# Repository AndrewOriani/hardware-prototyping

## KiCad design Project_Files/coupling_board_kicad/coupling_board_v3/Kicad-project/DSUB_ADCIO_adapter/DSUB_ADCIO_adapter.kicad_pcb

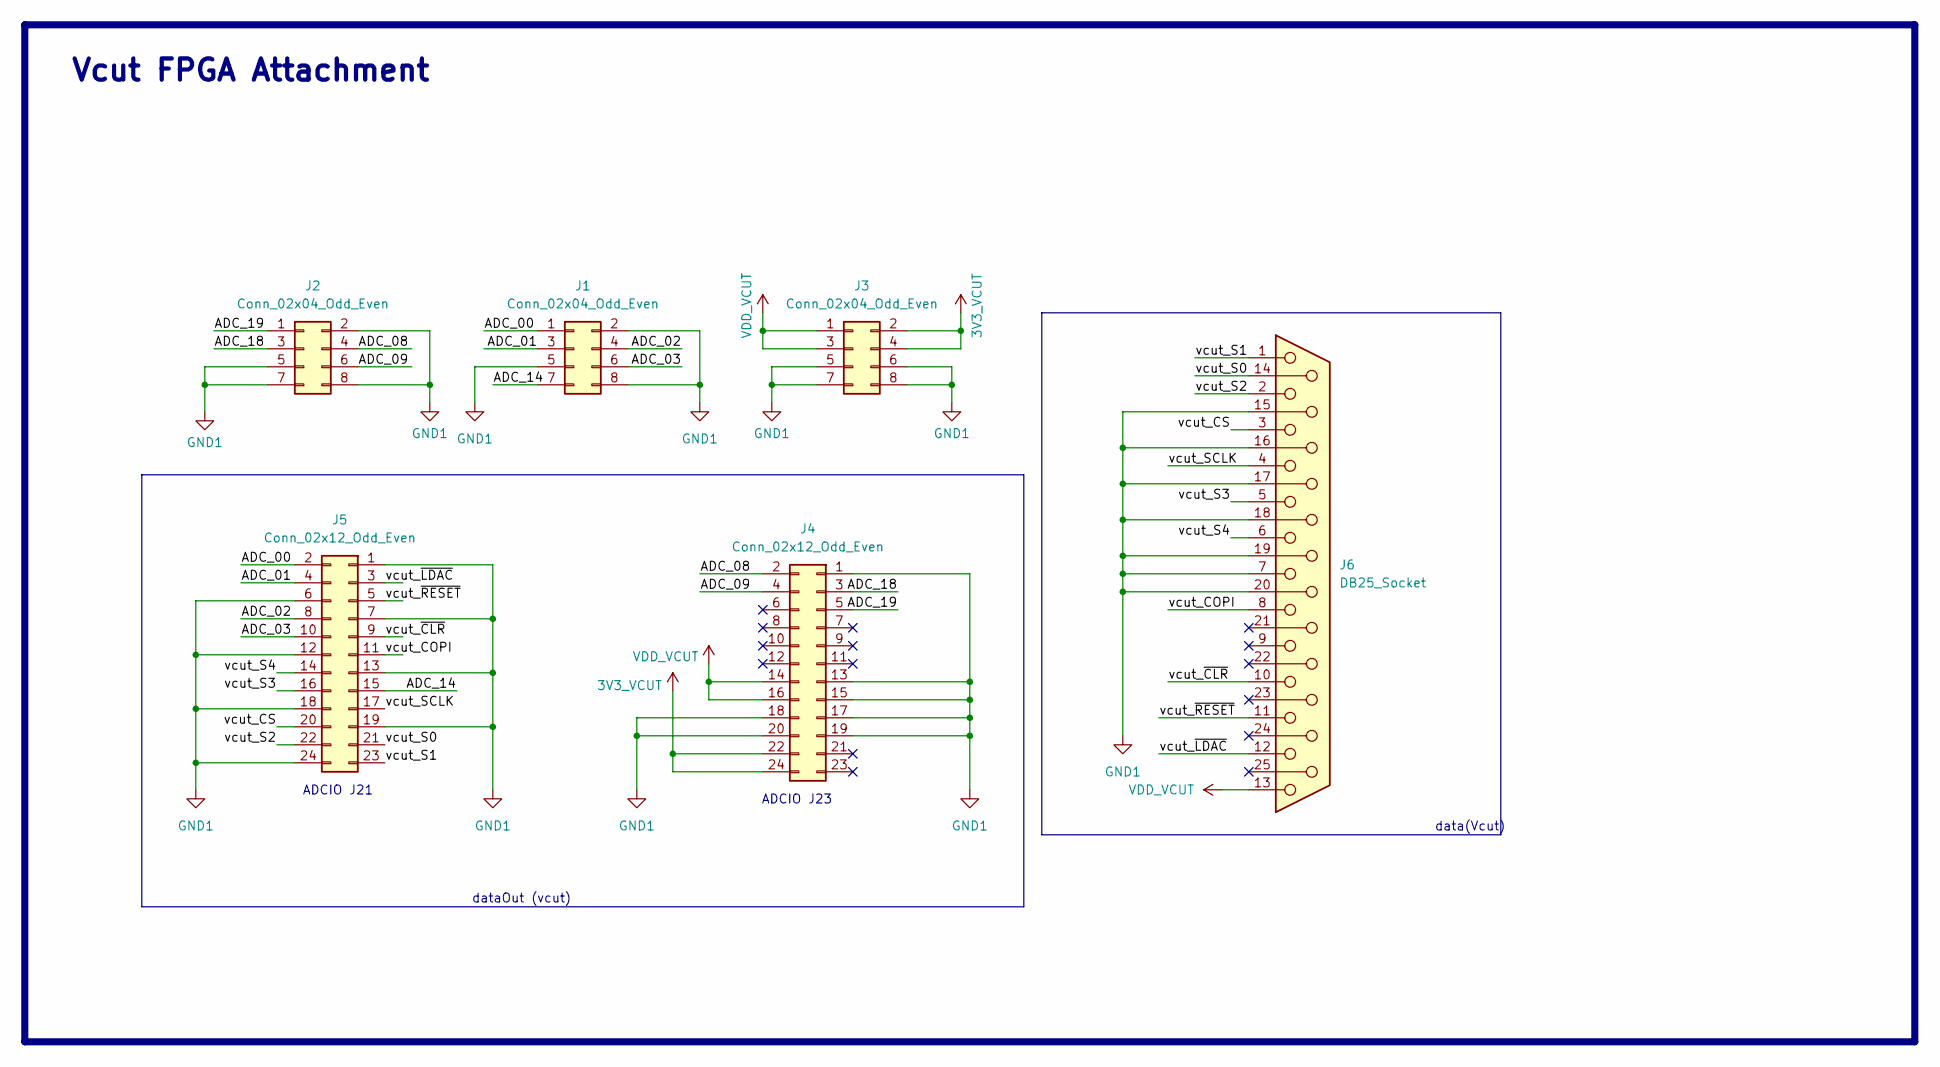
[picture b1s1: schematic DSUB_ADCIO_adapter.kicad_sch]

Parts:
J1, J2, J3: Conn_02x04_Odd_Even; PinSocket_2x04_P2.54mm_Vertical
J4, J5: Conn_02x12_Odd_Even; PinHeader_2x12_P2.54mm_Vertical; JLCPCB Part # C132440
J6: DB25_Socket; DSUB-TH_DS1034-25FUNSI44

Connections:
3V3_VCUT: J3.2, J3.4, J4.22, J4.24
/ADC_00: J1.1, J5.2
/ADC_01: J1.3, J5.4
/ADC_02: J1.4, J5.8
/ADC_03: J1.6, J5.10
/ADC_08: J2.4, J4.2
/ADC_09: J2.6, J4.4
/ADC_14: J1.7, J5.15
/ADC_18: J2.3, J4.3
/ADC_19: J2.1, J4.5
/vcut_COPI: J5.11, J6.8
/vcut_CS: J5.20, J6.3
/vcut_S0: J5.21, J6.14
/vcut_S1: J5.23, J6.1
/vcut_S2: J5.22, J6.2
/vcut_S3: J5.16, J6.5
/vcut_S4: J5.14, J6.6
/vcut_SCLK: J5.17, J6.4
/vcut_~CLR: J5.9, J6.10
/vcut_~LDAC: J5.3, J6.12
/vcut_~RESET: J5.5, J6.11
GND1: J1.2, J1.5, J1.8, J2.2, J2.5, J2.7, J2.8, J3.5, J3.6, J3.7, J3.8, J4.1, J4.13, J4.15, J4.17, J4.18, J4.19, J4.20, J5.1, J5.6, J5.7, J5.12, J5.13, J5.18, J5.19, J5.24, J6.7, J6.15, J6.16, J6.17, J6.18, J6.19, J6.20
VDD_VCUT: J3.1, J3.3, J4.14, J4.16, J6.13

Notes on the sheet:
ADCIO J23
data(Vcut)
ADCIO J21
Vcut FPGA Attachment
dataOut (vcut)

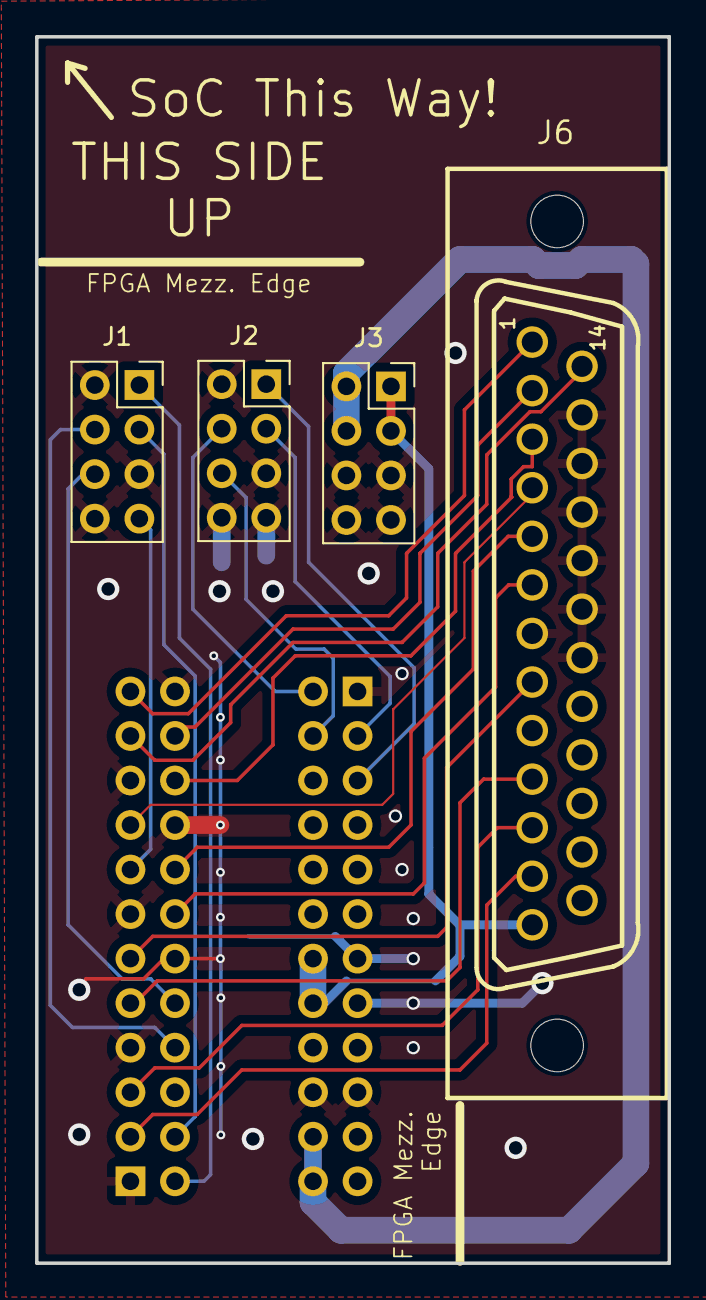
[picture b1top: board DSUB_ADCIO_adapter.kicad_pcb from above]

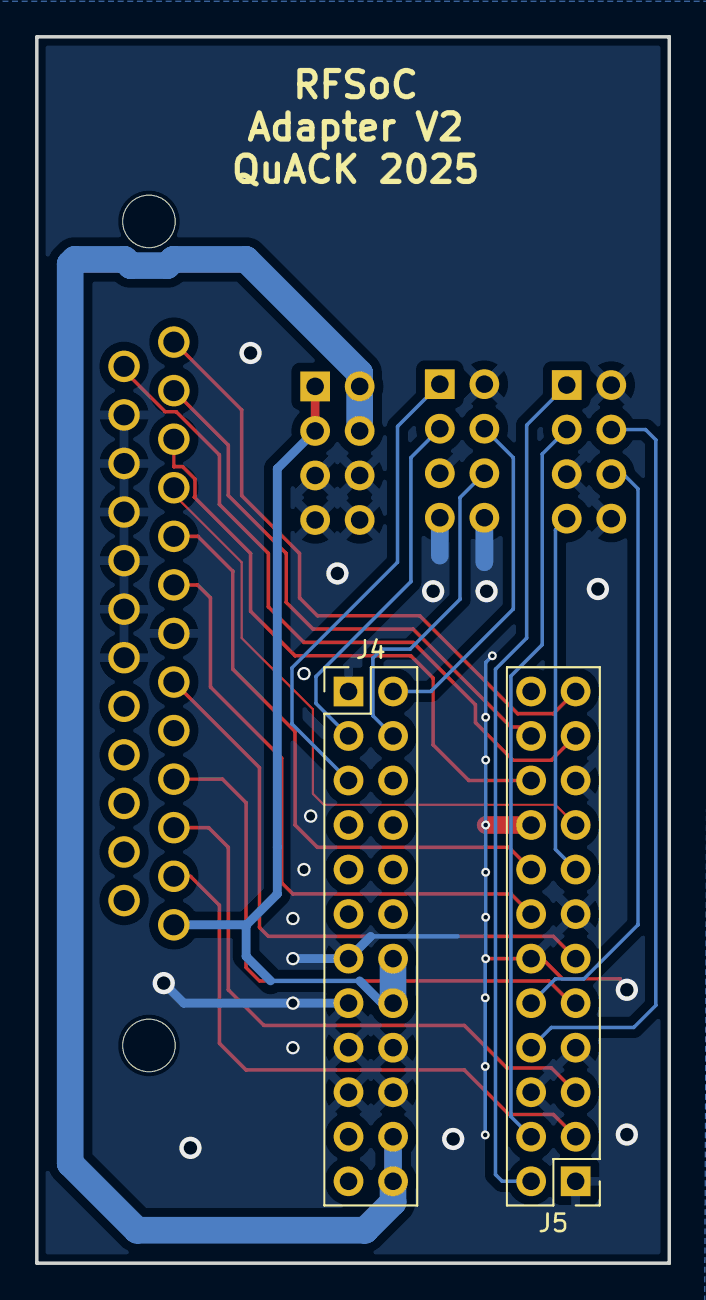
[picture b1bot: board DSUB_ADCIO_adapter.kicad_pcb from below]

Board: 2 copper layers, 36.1 x 70.0 mm, 6 parts (2 on the bottom side), 23 nets.

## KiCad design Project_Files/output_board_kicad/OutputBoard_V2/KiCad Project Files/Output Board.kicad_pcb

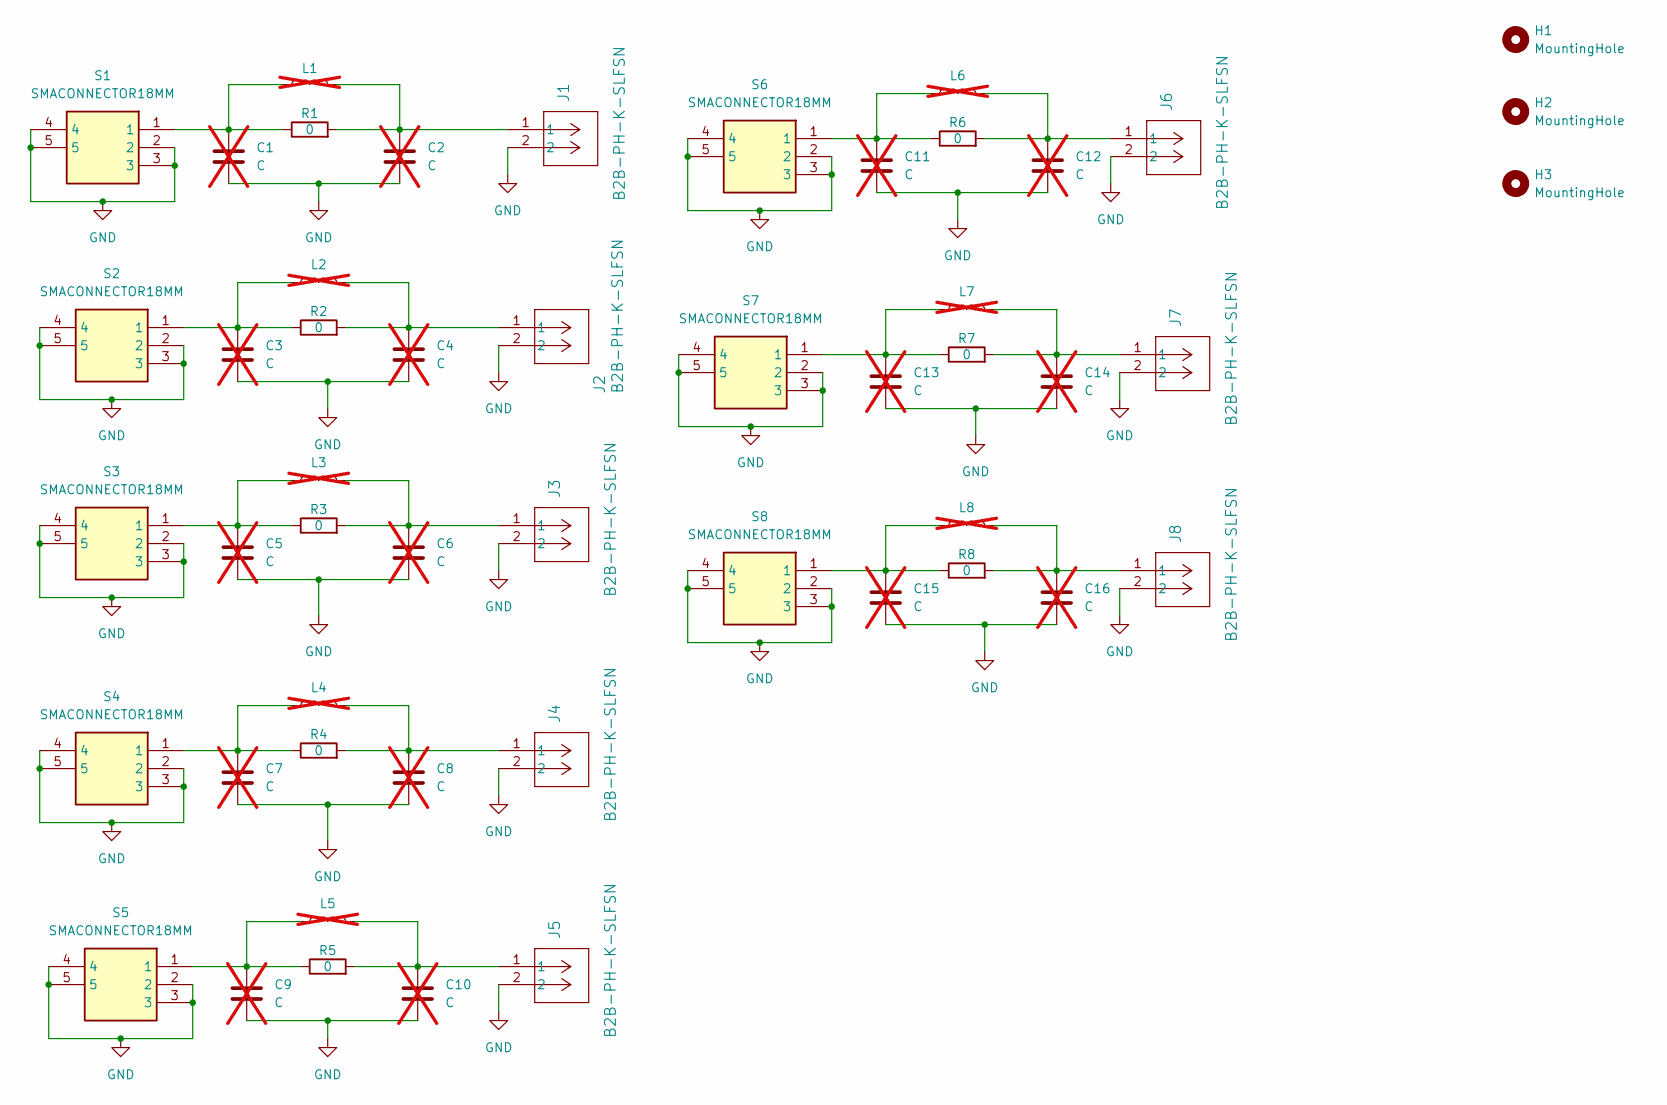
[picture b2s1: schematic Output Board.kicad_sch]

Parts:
C1, C2, C3, C4, C5, C6, C7, C8, C9, C10, C11, C12, C13, C14, C15, C16: C; C_0805_2012Metric; not fitted
H1, H2, H3: MountingHole; MountingHole_3mm
J1, J2, J3, J4, J5, J6, J7, J8: B2B-PH-K-SLFSN; CONN_B2B-PH-K-SLFSN_JST
L1, L2, L3, L4, L5, L6, L7, L8: L; IND_1537R_API; not fitted
R1, R2, R3, R4, R5, R6, R7, R8: 0; R_0805_2012Metric
S1, S2, S3, S4, S5, S6, S7, S8: SMACONNECTOR18MM; Mouser Part Number 471-SMACONNECTOR18MM

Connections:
GND: C1.2, C2.2, C3.2, C4.2, C5.2, C6.2, C7.2, C8.2, C9.2, C10.2, C11.2, C12.2, C13.2, C14.2, C15.2, C16.2, J1.2, J2.2, J3.2, J4.2, J5.2, J6.2, J7.2, J8.2, S1.2, S1.3, S1.4, S1.5, S2.2, S2.3, S2.4, S2.5, S3.2, S3.3, S3.4, S3.5, S4.2, S4.3, S4.4, S4.5, S5.2, S5.3, S5.4, S5.5, S6.2, S6.3, S6.4, S6.5, S7.2, S7.3, S7.4, S7.5, S8.2, S8.3, S8.4, S8.5
unnamed: C1.1, L1.1, R1.1, S1.1
unnamed: C2.1, J1.1, L1.2, R1.2
unnamed: C3.1, L2.1, R2.1, S2.1
unnamed: C4.1, J2.1, L2.2, R2.2
unnamed: C5.1, L3.1, R3.1, S3.1
unnamed: C6.1, J3.1, L3.2, R3.2
unnamed: C7.1, L4.1, R4.1, S4.1
unnamed: C8.1, J4.1, L4.2, R4.2
unnamed: C9.1, L5.1, R5.1, S5.1
unnamed: C10.1, J5.1, L5.2, R5.2
unnamed: C11.1, L6.1, R6.1, S6.1
unnamed: C12.1, J6.1, L6.2, R6.2
unnamed: C13.1, L7.1, R7.1, S7.1
unnamed: C14.1, J7.1, L7.2, R7.2
unnamed: C15.1, L8.1, R8.1, S8.1
unnamed: C16.1, J8.1, L8.2, R8.2

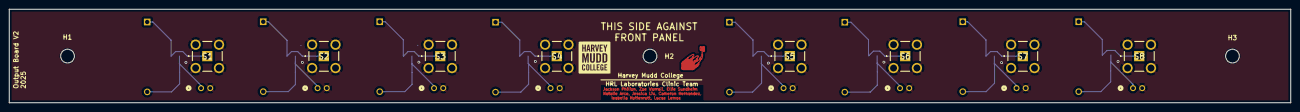
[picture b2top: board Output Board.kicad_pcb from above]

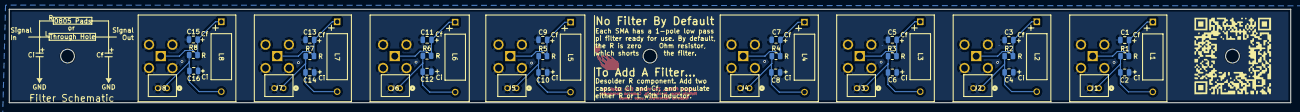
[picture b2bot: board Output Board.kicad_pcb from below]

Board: 2 copper layers, 279.4 x 20.4 mm, 52 parts (40 on the bottom side), 17 nets.

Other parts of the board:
  : LOGO; Footprint_HMC

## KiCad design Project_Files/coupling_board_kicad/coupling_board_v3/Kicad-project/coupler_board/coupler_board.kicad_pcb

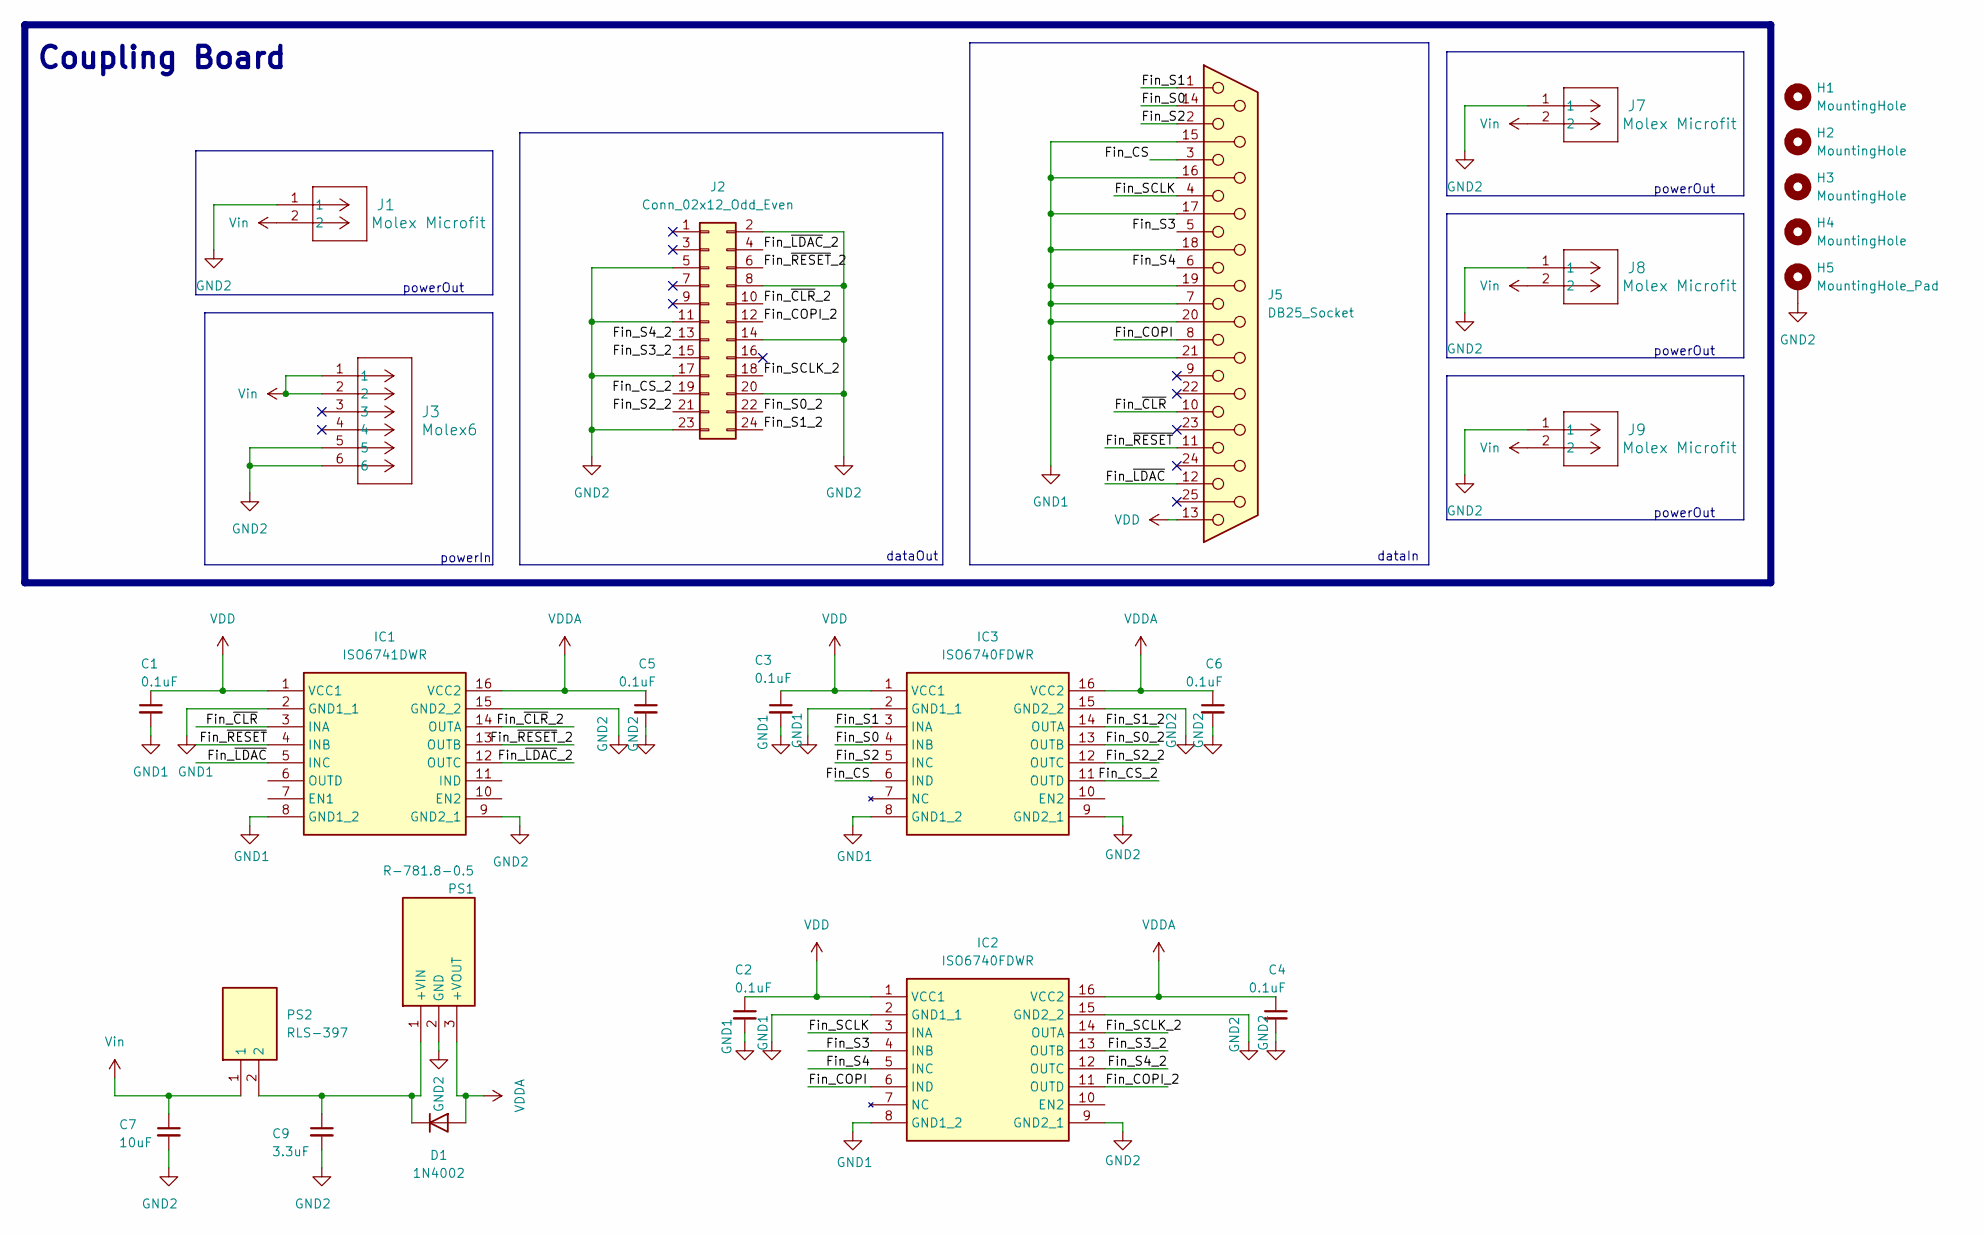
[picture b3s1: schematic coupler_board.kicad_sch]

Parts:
C1, C2, C3, C4, C5, C6: 0.1uF; C_0603_1608Metric
C7: 10uF; C_1210_3225Metric
C9: 3.3uF; C_1210_3225Metric
D1: 1N4002; D_DO-41_SOD81_P10.16mm_Horizontal
H1, H2, H3, H4: MountingHole; MountingHole_3.2mm_M3
H5: MountingHole_Pad; MountingHole_3.5mm_Pad
IC1: ISO6741DWR; SOIC127P1030X265-16N; Mouser Part Number 595-ISO6741DWR
IC2, IC3: ISO6740FDWR; SOIC127P1030X265-16N; Mouser Part Number 595-ISO6740FDWR
J1, J7, J8, J9: Molex Microfit; CONN_SD-43650-006_02_MOL
J2: Conn_02x12_Odd_Even; IDC-Header_2x12_P2.54mm_Vertical; JLCPCB Part # C132440
J3: Molex6; CONN_0039281063_5566-06A_MOL
J5: DB25_Socket; DSUB-TH_DS1034-25FUNSI44
PS1: R-781.8-0.5; R781805; Mouser Part Number 919-R-781.8-0.5
PS2: RLS-397; RLS397; Mouser Part Number 919-RLS-397

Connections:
/Fin_COPI: IC2.6 (IND), J5.8
/Fin_COPI_2: IC2.11 (OUTD), J2.12
/Fin_CS: IC3.6 (IND), J5.3
/Fin_CS_2: IC3.11 (OUTD), J2.19
/Fin_S0: IC3.4 (INB), J5.14
/Fin_S0_2: IC3.13 (OUTB), J2.22
/Fin_S1: IC3.3 (INA), J5.1
/Fin_S1_2: IC3.14 (OUTA), J2.24
/Fin_S2: IC3.5 (INC), J5.2
/Fin_S2_2: IC3.12 (OUTC), J2.21
/Fin_S3: IC2.4 (INB), J5.5
/Fin_S3_2: IC2.13 (OUTB), J2.15
/Fin_S4: IC2.5 (INC), J5.6
/Fin_S4_2: IC2.12 (OUTC), J2.13
/Fin_SCLK: IC2.3 (INA), J5.4
/Fin_SCLK_2: IC2.14 (OUTA), J2.18
/Fin_~CLR: IC1.3 (INA), J5.10
/Fin_~CLR_2: IC1.14 (OUTA), J2.10
/Fin_~LDAC: IC1.5 (INC), J5.12
/Fin_~LDAC_2: IC1.12 (OUTC), J2.4
/Fin_~RESET: IC1.4 (INB), J5.11
/Fin_~RESET_2: IC1.13 (OUTB), J2.6
GND1: C1.2, C2.2, C3.2, IC1.2 (GND1_1), IC1.8 (GND1_2), IC2.2 (GND1_1), IC2.8 (GND1_2), IC3.2 (GND1_1), IC3.8 (GND1_2), J5.7, J5.15, J5.16, J5.17, J5.18, J5.19, J5.20, J5.21
GND2: C4.2, C5.2, C6.2, C7.2, C9.2, H5.1, IC1.9 (GND2_1), IC1.15 (GND2_2), IC2.9 (GND2_1), IC2.15 (GND2_2), IC3.9 (GND2_1), IC3.15 (GND2_2), J1.1, J2.2, J2.5, J2.8, J2.11, J2.14, J2.17, J2.20, J2.23, J3.5, J3.6, J7.1, J8.1, J9.1, PS1.2 (GND)
unnamed: C9.1, D1.1 (K), PS1.1 (+VIN), PS2.2
VDD: C1.1, C2.1, C3.1, IC1.1 (VCC1), IC2.1 (VCC1), IC3.1 (VCC1), J5.13
VDDA: C4.1, C5.1, C6.1, D1.2 (A), IC1.16 (VCC2), IC2.16 (VCC2), IC3.16 (VCC2), PS1.3 (+VOUT)
Vin: C7.1, J1.2, J3.1, J3.2, J7.2, J8.2, J9.2, PS2.1

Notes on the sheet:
powerOut
dataIn
dataOut
powerIn
Coupling Board

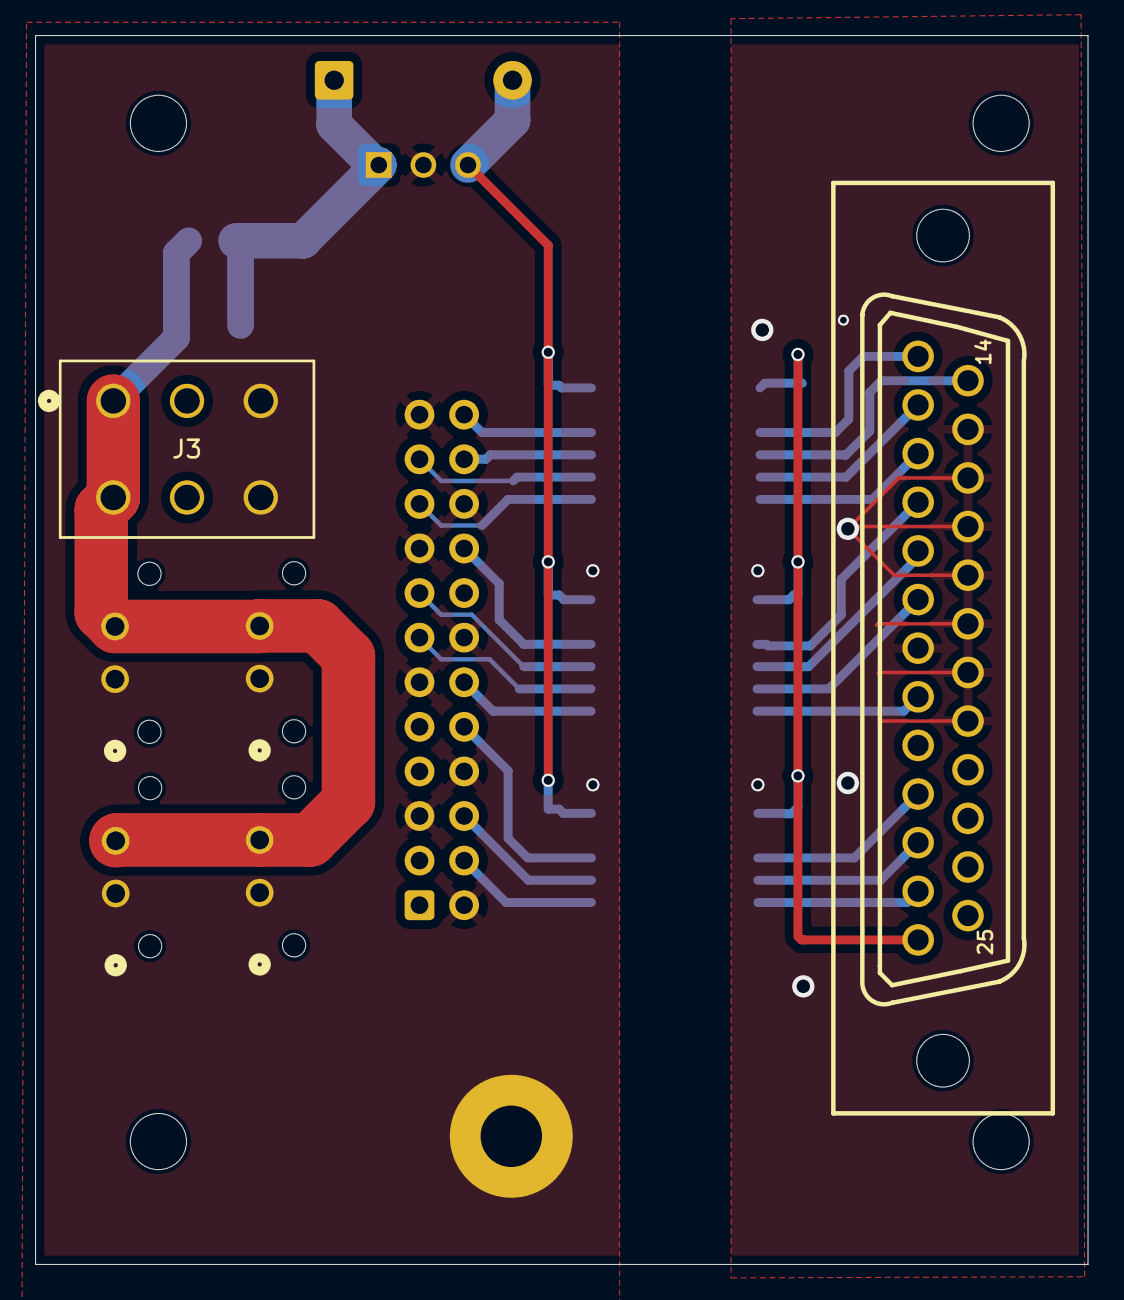
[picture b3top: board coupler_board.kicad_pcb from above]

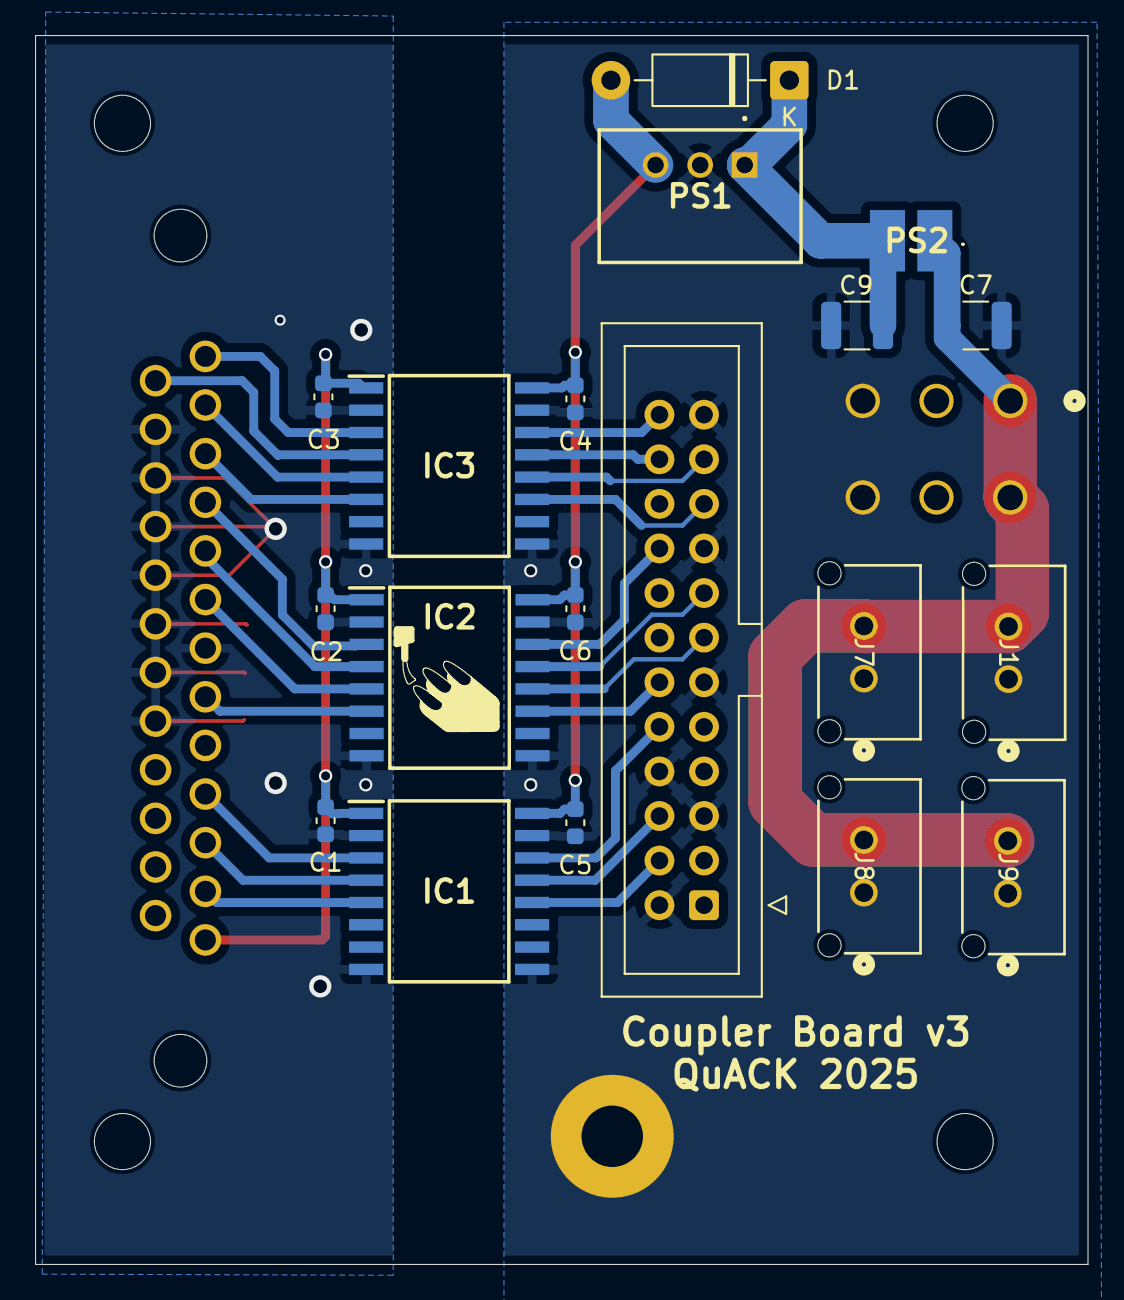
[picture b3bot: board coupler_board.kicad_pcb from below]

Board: 2 copper layers, 59.9 x 70.0 mm, 26 parts (19 on the bottom side), 28 nets.

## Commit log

2025-07-29 Added a v3 isolated version of coupler board, still need to add BOM and other project files
2025-08-04 Updated design files
2025-08-04 Updated design, added digikey bom
2025-08-04 Updated design
2025-08-05 Committing prototyped DRC checked version
2025-08-09 Reorganized output board, fixed grounding
2025-08-11 Updated gerber and BOMs
2025-08-14 Updated GRB with DRL
2025-09-18 Fixed adcio coupler
2025-11-27 Random commit
